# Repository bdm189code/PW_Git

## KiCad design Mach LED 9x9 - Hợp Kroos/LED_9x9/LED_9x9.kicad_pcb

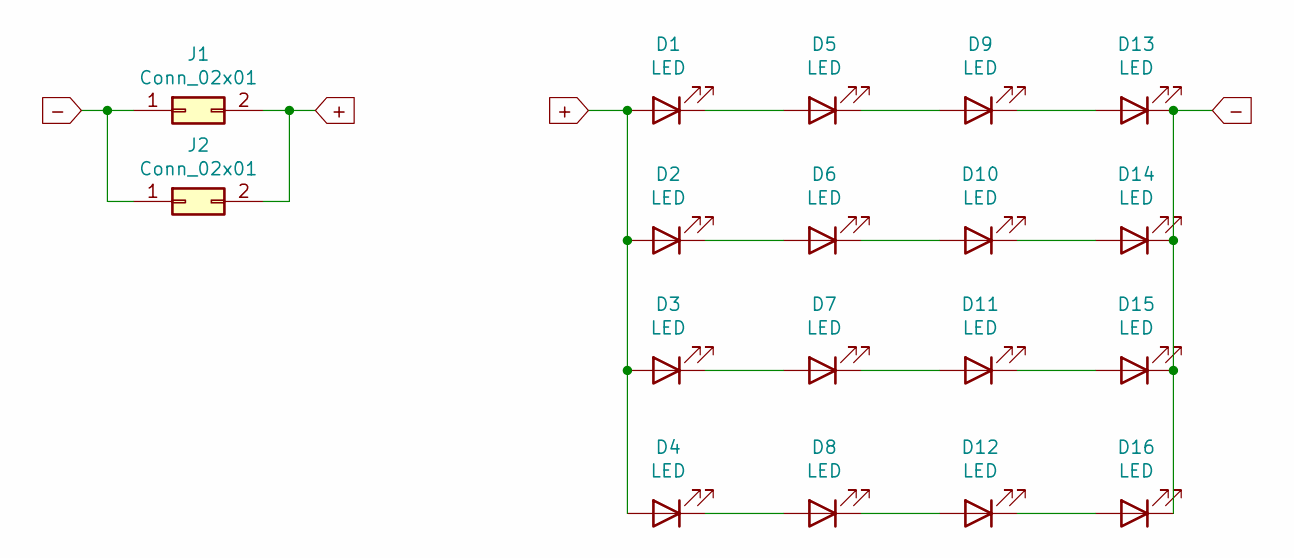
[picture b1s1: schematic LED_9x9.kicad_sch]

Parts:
D1, D2, D3, D4, D5, D6, D7, D8, D9, D10, D11, D12, D13, D14, D15, D16: LED; LED_1W_3W_R8
J1, J2: Conn_02x01; SMD_POW

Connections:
+: D1.2 (A), D2.2 (A), D3.2 (A), D4.2 (A), J1.2, J2.2
-: D13.1 (K), D14.1 (K), D15.1 (K), D16.1 (K), J1.1, J2.1
unnamed: D1.1 (K), D5.2 (A)
unnamed: D2.1 (K), D6.2 (A)
unnamed: D3.1 (K), D7.2 (A)
unnamed: D4.1 (K), D8.2 (A)
unnamed: D5.1 (K), D9.2 (A)
unnamed: D10.1 (K), D14.2 (A)
unnamed: D6.1 (K), D10.2 (A)
unnamed: D11.1 (K), D15.2 (A)
unnamed: D7.1 (K), D11.2 (A)
unnamed: D12.1 (K), D16.2 (A)
unnamed: D8.1 (K), D12.2 (A)
unnamed: D9.1 (K), D13.2 (A)

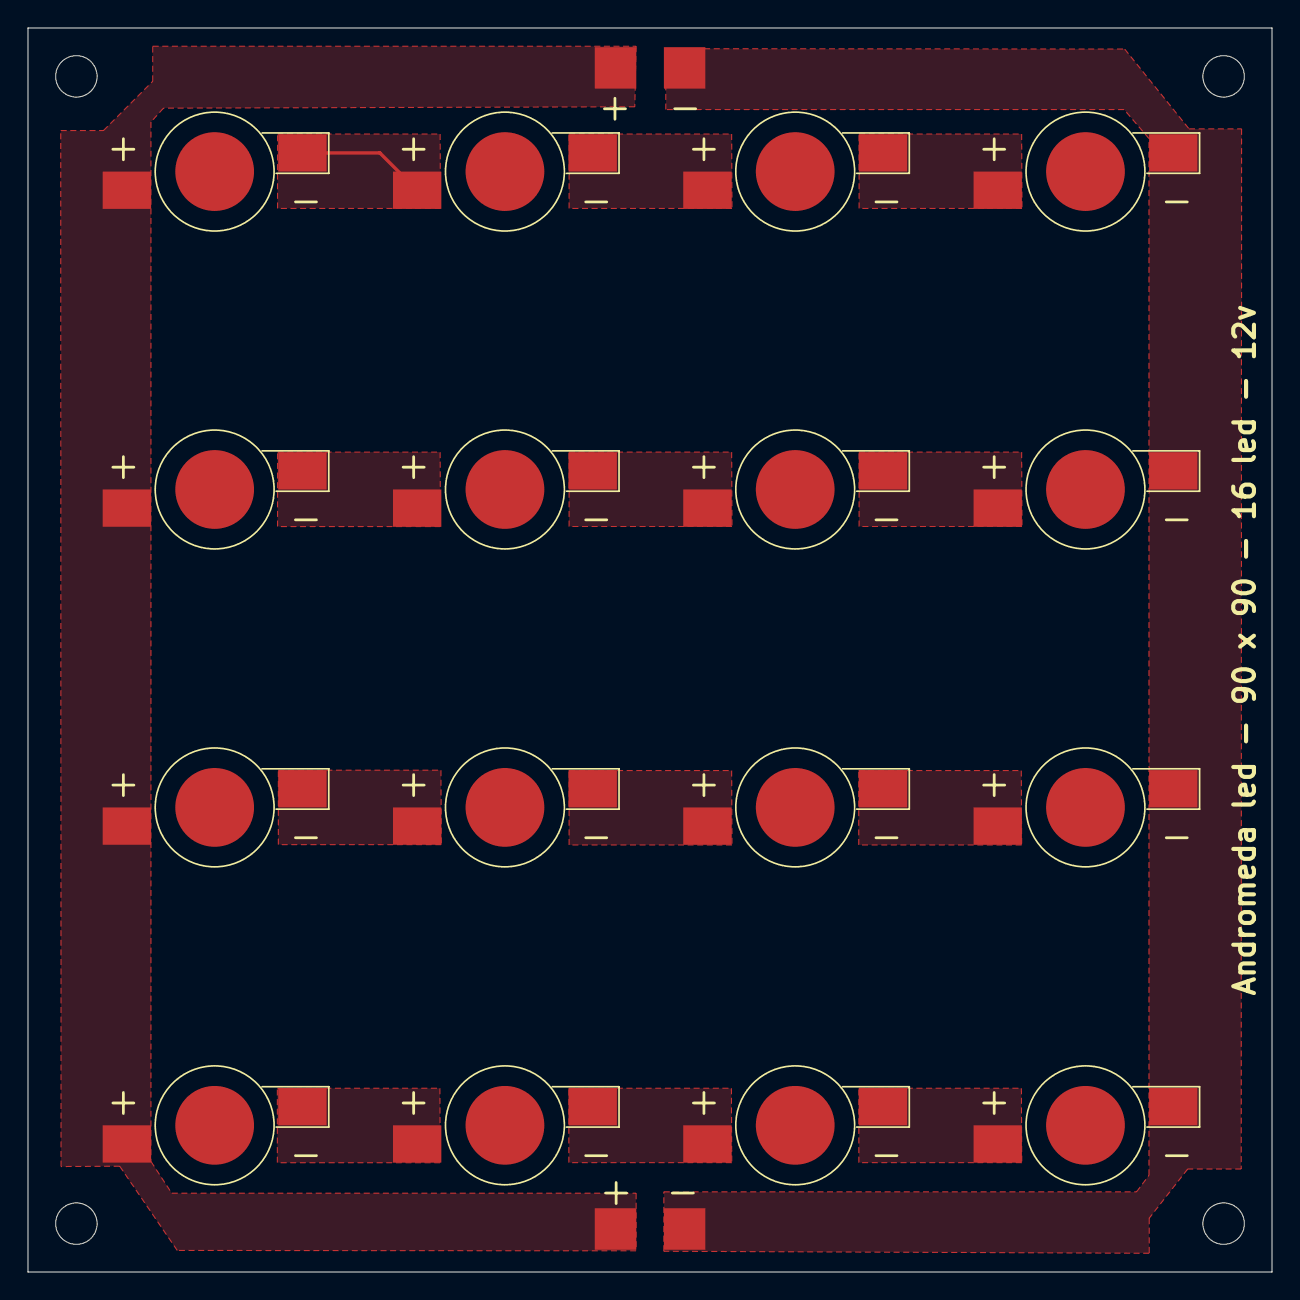
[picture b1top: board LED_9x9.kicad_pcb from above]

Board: 2 copper layers, 90.0 x 90.0 mm, 18 parts (0 on the bottom side), 14 nets.
